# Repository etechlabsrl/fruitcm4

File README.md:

# Salmonberry Pi, Fruit \ 'früt \

> The Raspberry Pi is a series of credit card-sized single-board computers developed in the United Kingdom by the Raspberry Pi Foundation to promote the teaching of basic computer science in schools and developing countries. Official Link: [Raspberry Pi Foundation Homepage](https://raspberrypi.org), [Raspberry Pi Computer Homepage](https://www.raspberrypi.com)

<p>

Salmonberry Pi is a group of open source hardware projects which allow the construction of cluster hardware from small to arbitrary size using Raspberry Pi platforms.  This includes the Raspberry Pi Compute Module 4 (CM4) Raspberry Pi Zero 2 W, Raspberry Pi 4 Model B, and Raspberry Pi RP2040 microcontrollers.

The goals of this project are to provide:
- infrastructure for clustering nodes
- self-sufficient nodes by default (no 'leader')
- remotely monitoring
- remote management
- standard form factors and connectors, although perhaps repurposed

The component projects are:
- [Face CM4](https://github.com/salmonberrypi/facecm4), 8TE 3U faceplate with jacks, microSD card slot and LEDs.
- [Fruit CM4](https://github.com/salmonberrypi/fruitcm4), carrier board for CM4, general purpose compute or storage or both.
- [Graft](https://github.com/salmonberrypi/graft), development board to bring up Fruit board, allows diversion to on-board connectors for rhizome served power and signals. Can be used with or without rhizome boards. (out of date)
- [Thorn](https://github.com/salmonberrypi/thorn), passive board to protect the male plug on the Fruit or Graft boards. (out of date)
- [Rhizome](https://github.com/salmonberrypi/rhizome), life support systems and connectivity
- [Stem 3U x 160mm](https://github.com/salmonberrypi/stem_3U_160mm_X4), 3U x 160mm passive slot extension for debugging

(images are from a previous revision and out of date, shown for reference)

PCB front:

PCB back:

Dimensions: 160 x 100mm (0.562 x 0.478 [bananas](http://bananaforscale.info/#!/convert/length/bananas/millimeters)) without connector and faceplate, 4 layer PCB (pwr/signal, gnd, gnd, pwr/signal).

Review [Interactive BOM](https://htmlpreview.github.io/?https://raw.githubusercontent.com/salmonberrypi/fruitcm4/main/artifacts/bom/ibom.html).

Review [Schematic](https://github.com/salmonberrypi/fruitcm4/blob/main/artifacts/fruitcm4%20schematic.pdf).

---

Designed in [KiCad 6](https://kicad.org) on [Ubuntu](https://ubuntu.org) 21.10 (impish).

---

Raspberry Pi is a trademark of Raspberry Pi Trading

---

Copyright (C) 2022 Christian Kuhtz

This source describes Open Hardware and is licensed under the CERN-OHLW v2
<P>
You may redistribute and modify this documentation and make products
using it under the terms of the CERN-OHL-W v2 (https:/cern.ch/cern-ohl).
<P>
This documentation is distributed WITHOUT ANY EXPRESS OR IMPLIED
WARRANTY, INCLUDING OF MERCHANTABILITY, SATISFACTORY QUALITY
AND FITNESS FOR A PARTICULAR PURPOSE. Please see the <a href="https://ohwr.org/cern_ohl_w_v2.txt">CERN-OHL-W v2</a> for applicable conditions.
<P>
Source location: https://github.com/salmonberrypi
<P>
As per CERN-OHL-W v2 section 4.1, should You produce hardware based on
these sources, You must maintain the Source Location visible on the
external case of the Salmonberry Pi or other product you make using
this documentation.

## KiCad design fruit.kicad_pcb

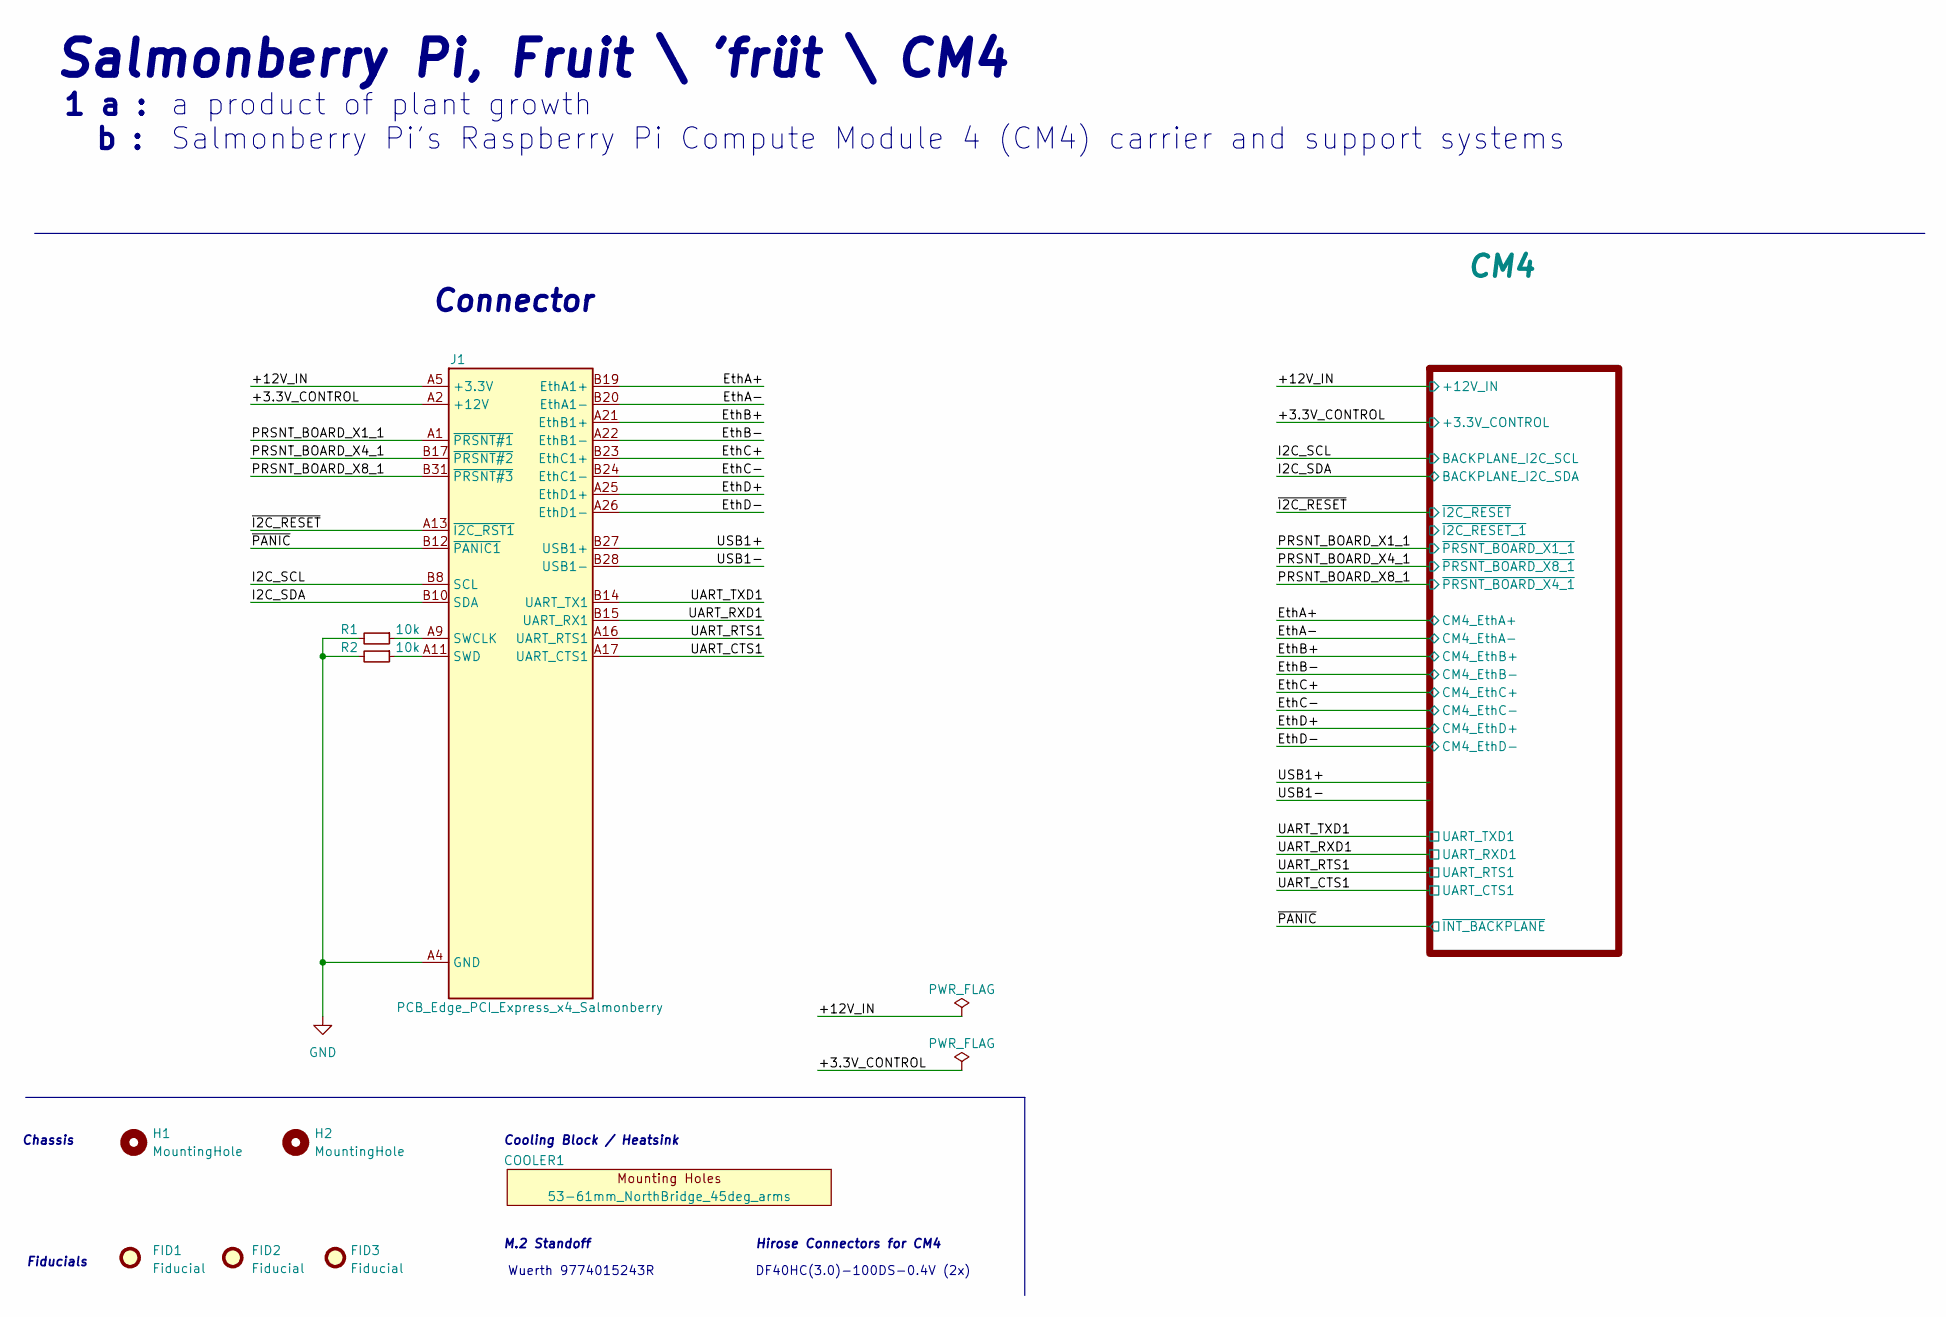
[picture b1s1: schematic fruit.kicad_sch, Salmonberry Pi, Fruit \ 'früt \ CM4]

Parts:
COOLER1: 53-61mm_NorthBridge_45deg_arms
FID1, FID2, FID3: Fiducial; Fiducial_1mm_Mask2mm
H1, H2: MountingHole; MountingHole_2.7mm_M2.5
J1: PCB_Edge_PCI_Express_x4_Salmonberry; BUS_PCIexpress_x4_Salmonberry_reduced_shoulders
R1, R2: 10k; R_0402_1005Metric

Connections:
+3.3V: J1.A5 (+3.3V), J1.A6 (+3.3V), J1.B5 (+3.3V), J1.B6 (+3.3V); also elsewhere on the board
+12V: J1.A2 (+12V), J1.A3 (+12V), J1.B1 (+12V), J1.B2 (+12V), J1.B3 (+12V); also elsewhere on the board
/EthA+: J1.B19 (EthA1+); also elsewhere on the board
/EthA-: J1.B20 (EthA1-); also elsewhere on the board
/EthB+: J1.A21 (EthB1+); also elsewhere on the board
/EthB-: J1.A22 (EthB1-); also elsewhere on the board
/EthC+: J1.B23 (EthC1+); also elsewhere on the board
/EthC-: J1.B24 (EthC1-); also elsewhere on the board
/EthD+: J1.A25 (EthD1+); also elsewhere on the board
/EthD-: J1.A26 (EthD1-); also elsewhere on the board
/I2C_SCL: J1.B8 (SCL); also elsewhere on the board
/I2C_SDA: J1.B10 (SDA); also elsewhere on the board
/PRSNT_BOARD_X1_1: J1.A1 (~PRSNT#1); also elsewhere on the board
/PRSNT_BOARD_X4_1: J1.B17 (~PRSNT#2); also elsewhere on the board
/PRSNT_BOARD_X8_1: J1.B31 (~PRSNT#3); also elsewhere on the board
/UART_CTS1: J1.A17 (UART_CTS1); also elsewhere on the board
/UART_RTS1: J1.A16 (UART_RTS1); also elsewhere on the board
/UART_RXD1: J1.B15 (UART_RX1); also elsewhere on the board
/UART_TXD1: J1.B14 (UART_TX1); also elsewhere on the board
/USB1+: J1.B27 (USB1+)
/USB1-: J1.B28 (USB1-)
/~I2C_RESET: J1.A13 (~I2C_RST1); also elsewhere on the board
/~PANIC: J1.B12 (~PANIC1); also elsewhere on the board
GND: J1.A4 (GND), J1.A7 (GND), J1.A8 (GND), J1.A10 (GND), J1.A12 (GND), J1.A14 (GND), J1.A15 (GND), J1.A18 (GND), J1.A19 (GND), J1.A20 (GND), J1.A23 (GND), J1.A24 (GND), J1.A27 (GND), J1.A28 (GND), J1.A29 (GND), J1.A30 (GND), J1.A31 (GND), J1.A32 (GND), J1.B4 (GND), J1.B7 (GND), J1.B9 (GND), J1.B11 (GND), J1.B13 (GND), J1.B16 (GND), J1.B18 (GND), J1.B21 (GND), J1.B22 (GND), J1.B25 (GND), J1.B26 (GND), J1.B29 (GND), J1.B30 (GND), J1.B32 (GND), R1.2, R2.2; also elsewhere on the board
unnamed: J1.A9 (SWCLK), R1.1
unnamed: J1.A11 (SWD), R2.1

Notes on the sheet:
Cooling Block / Heatsink
M.2 Standoff
Salmonberry Pi, Fruit \ 'früt \ CM4
Fiducials
1 a : b :
a product of plant growth Salmonberry Pi's Raspberry Pi Compute Module 4 (CM4) carrier and support systems
Hirose Connectors for CM4
DF40HC(3.0)-100DS-0.4V (2x)
Chassis
Wuerth 9774015243R
Connector

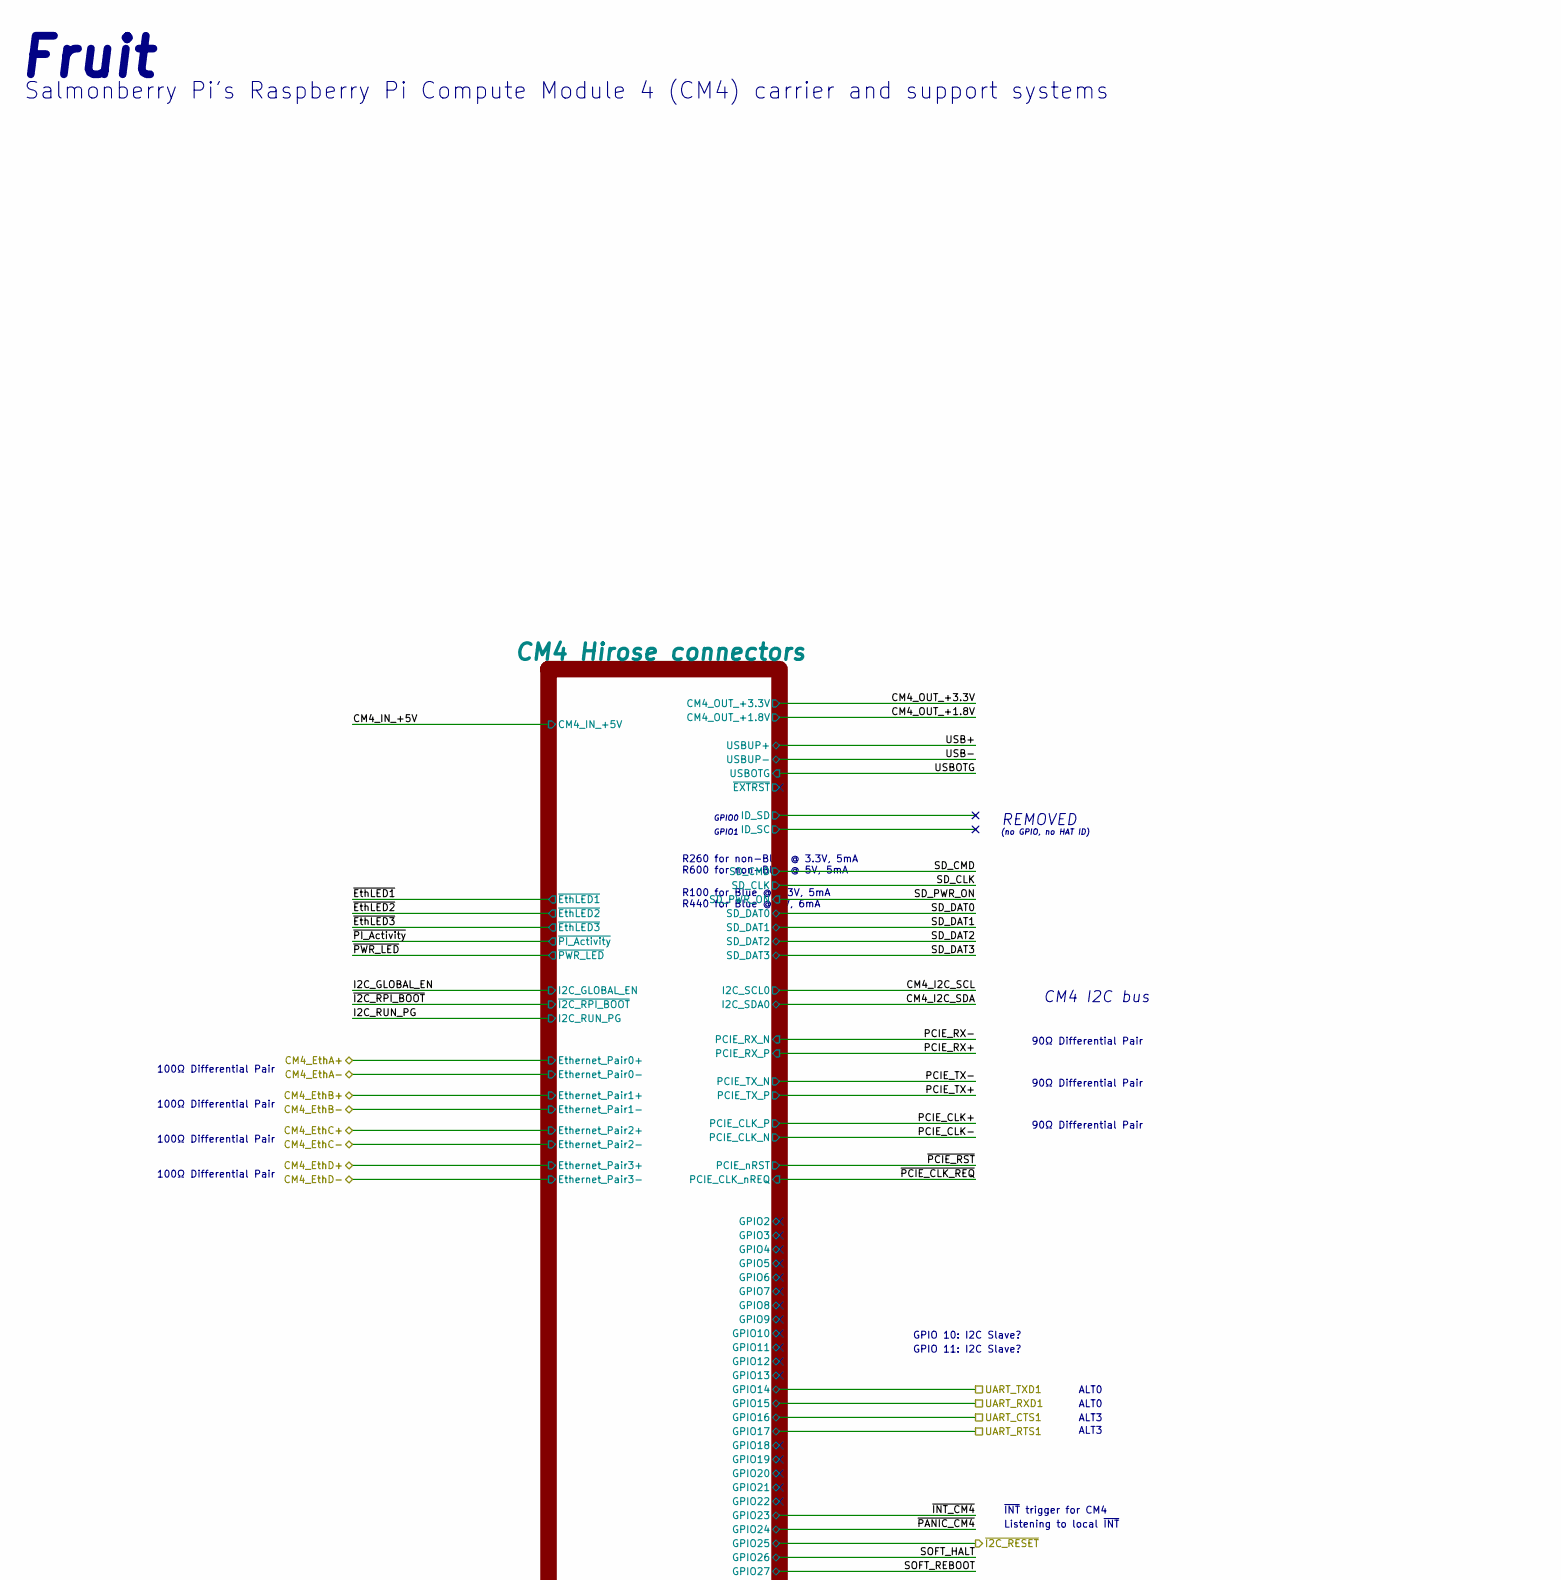
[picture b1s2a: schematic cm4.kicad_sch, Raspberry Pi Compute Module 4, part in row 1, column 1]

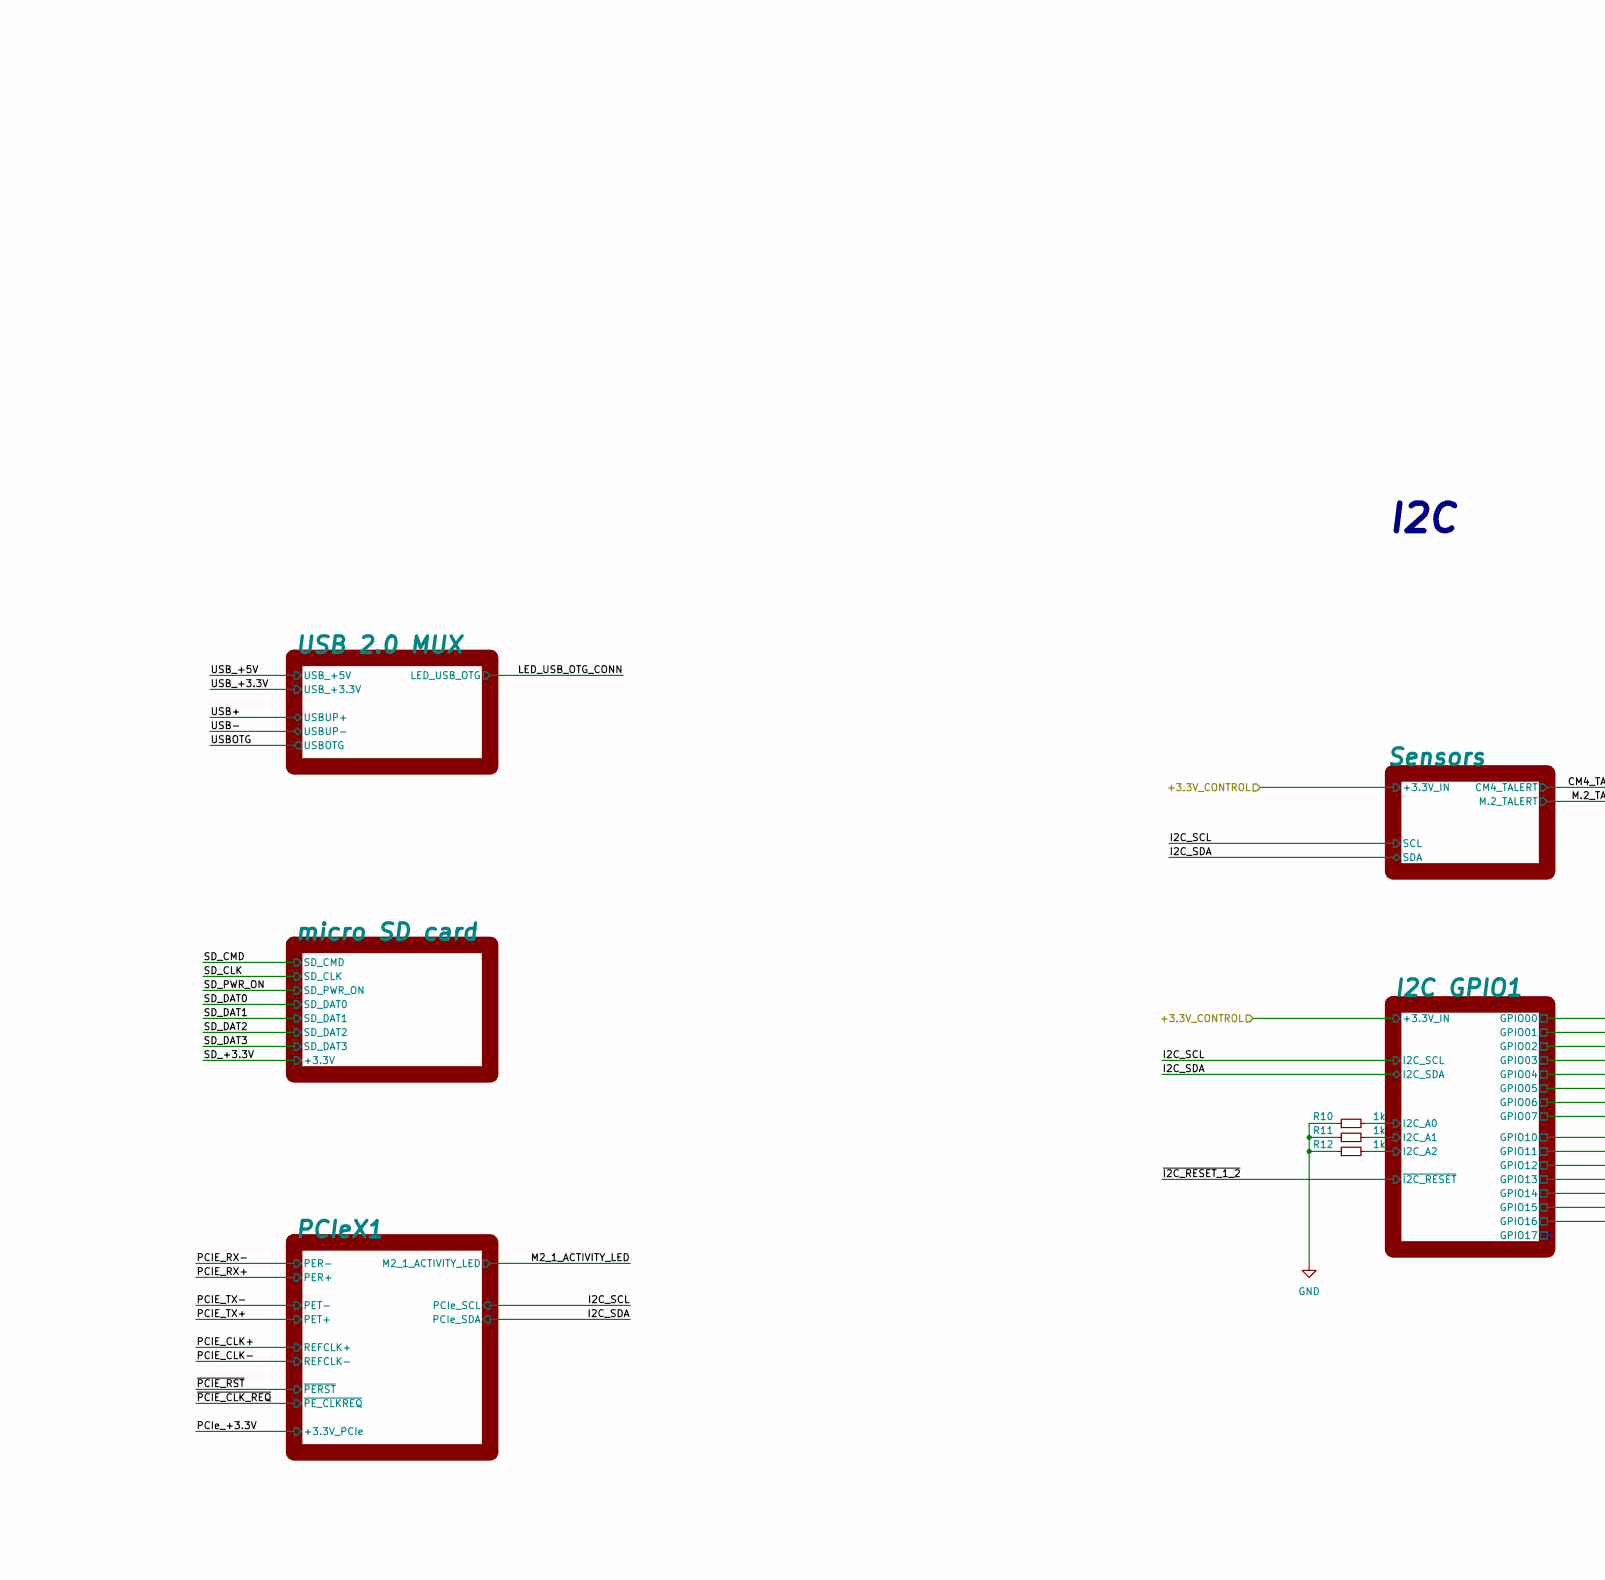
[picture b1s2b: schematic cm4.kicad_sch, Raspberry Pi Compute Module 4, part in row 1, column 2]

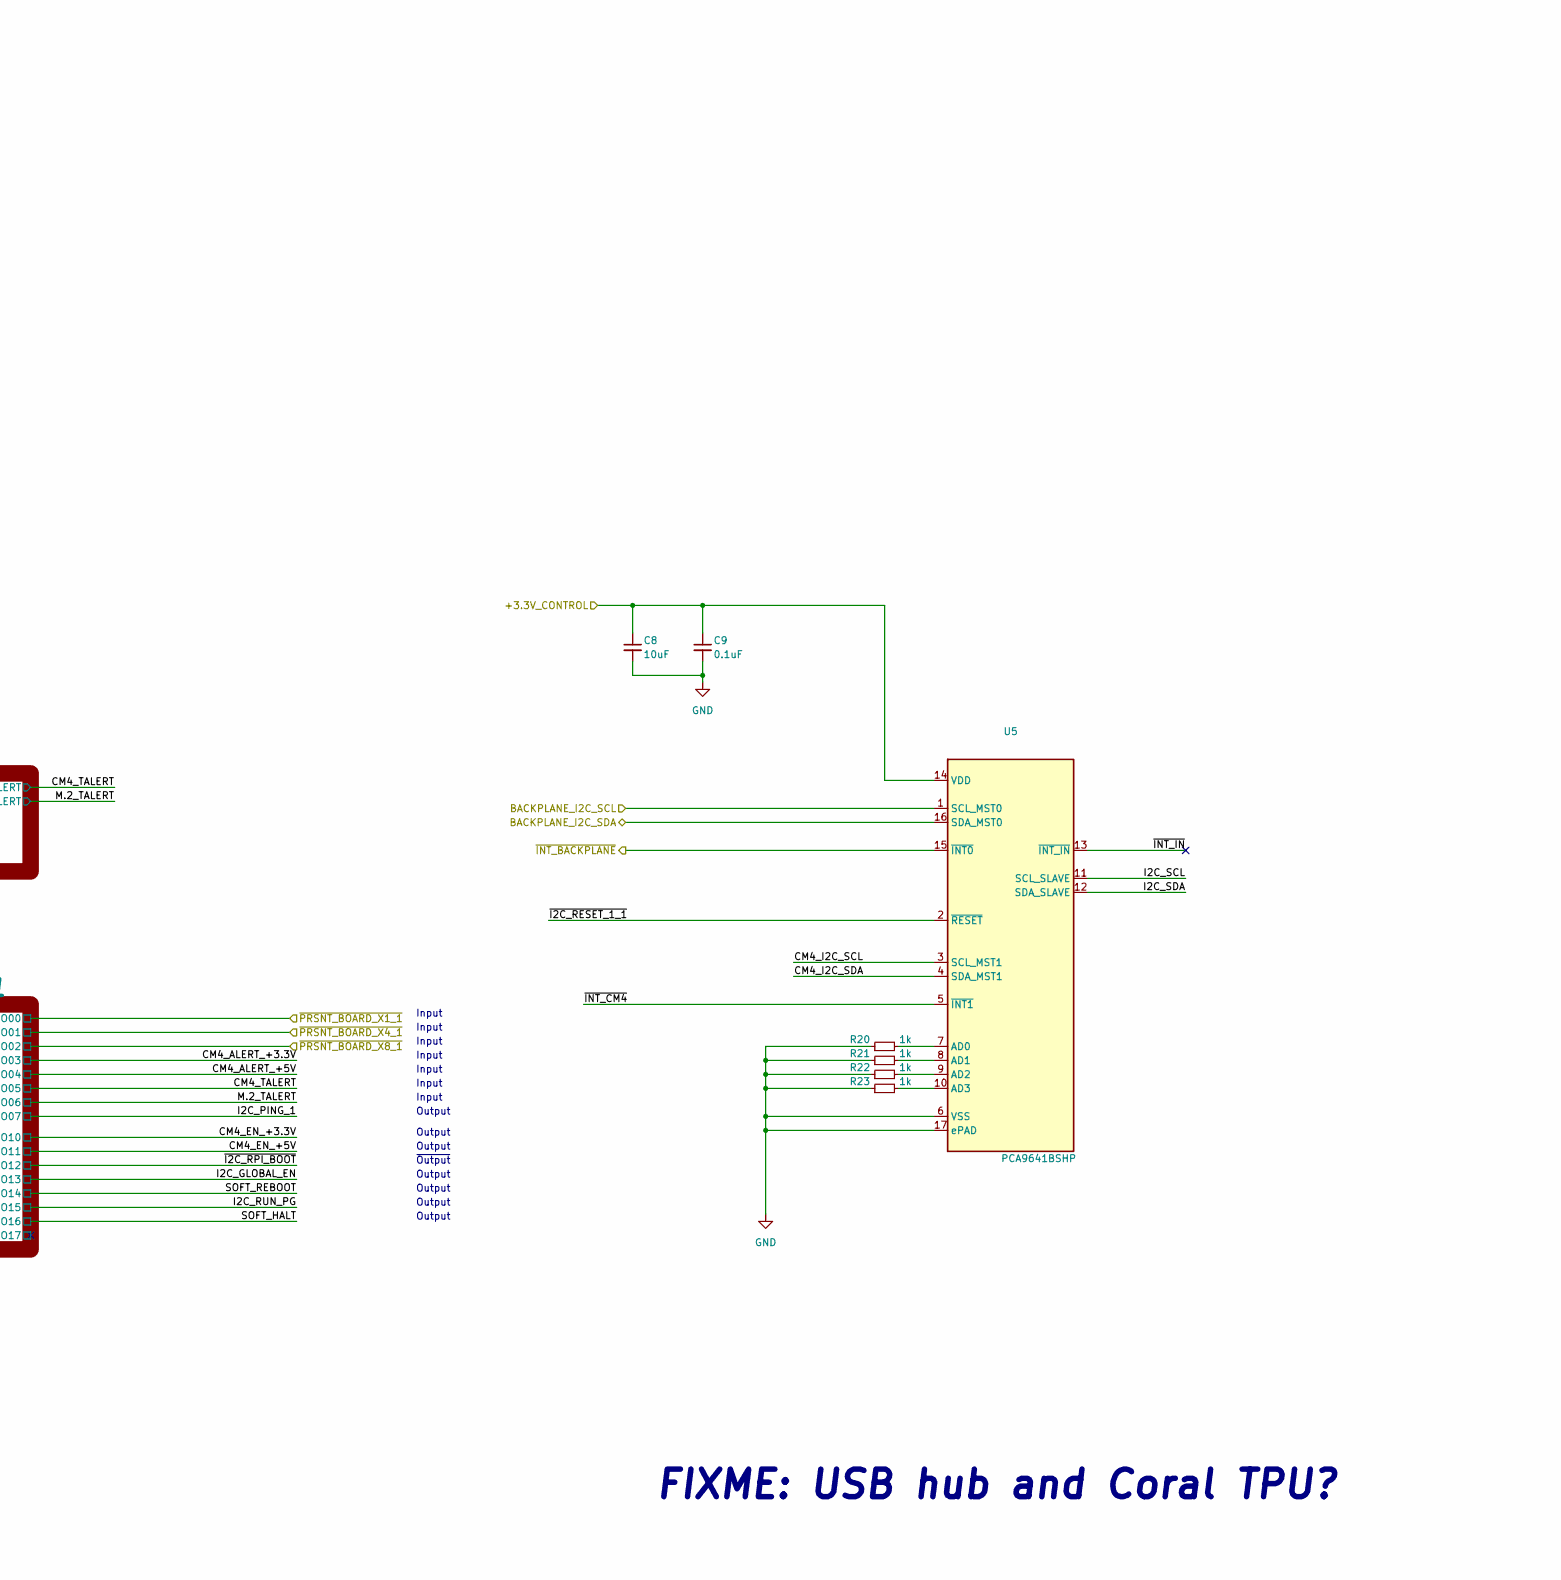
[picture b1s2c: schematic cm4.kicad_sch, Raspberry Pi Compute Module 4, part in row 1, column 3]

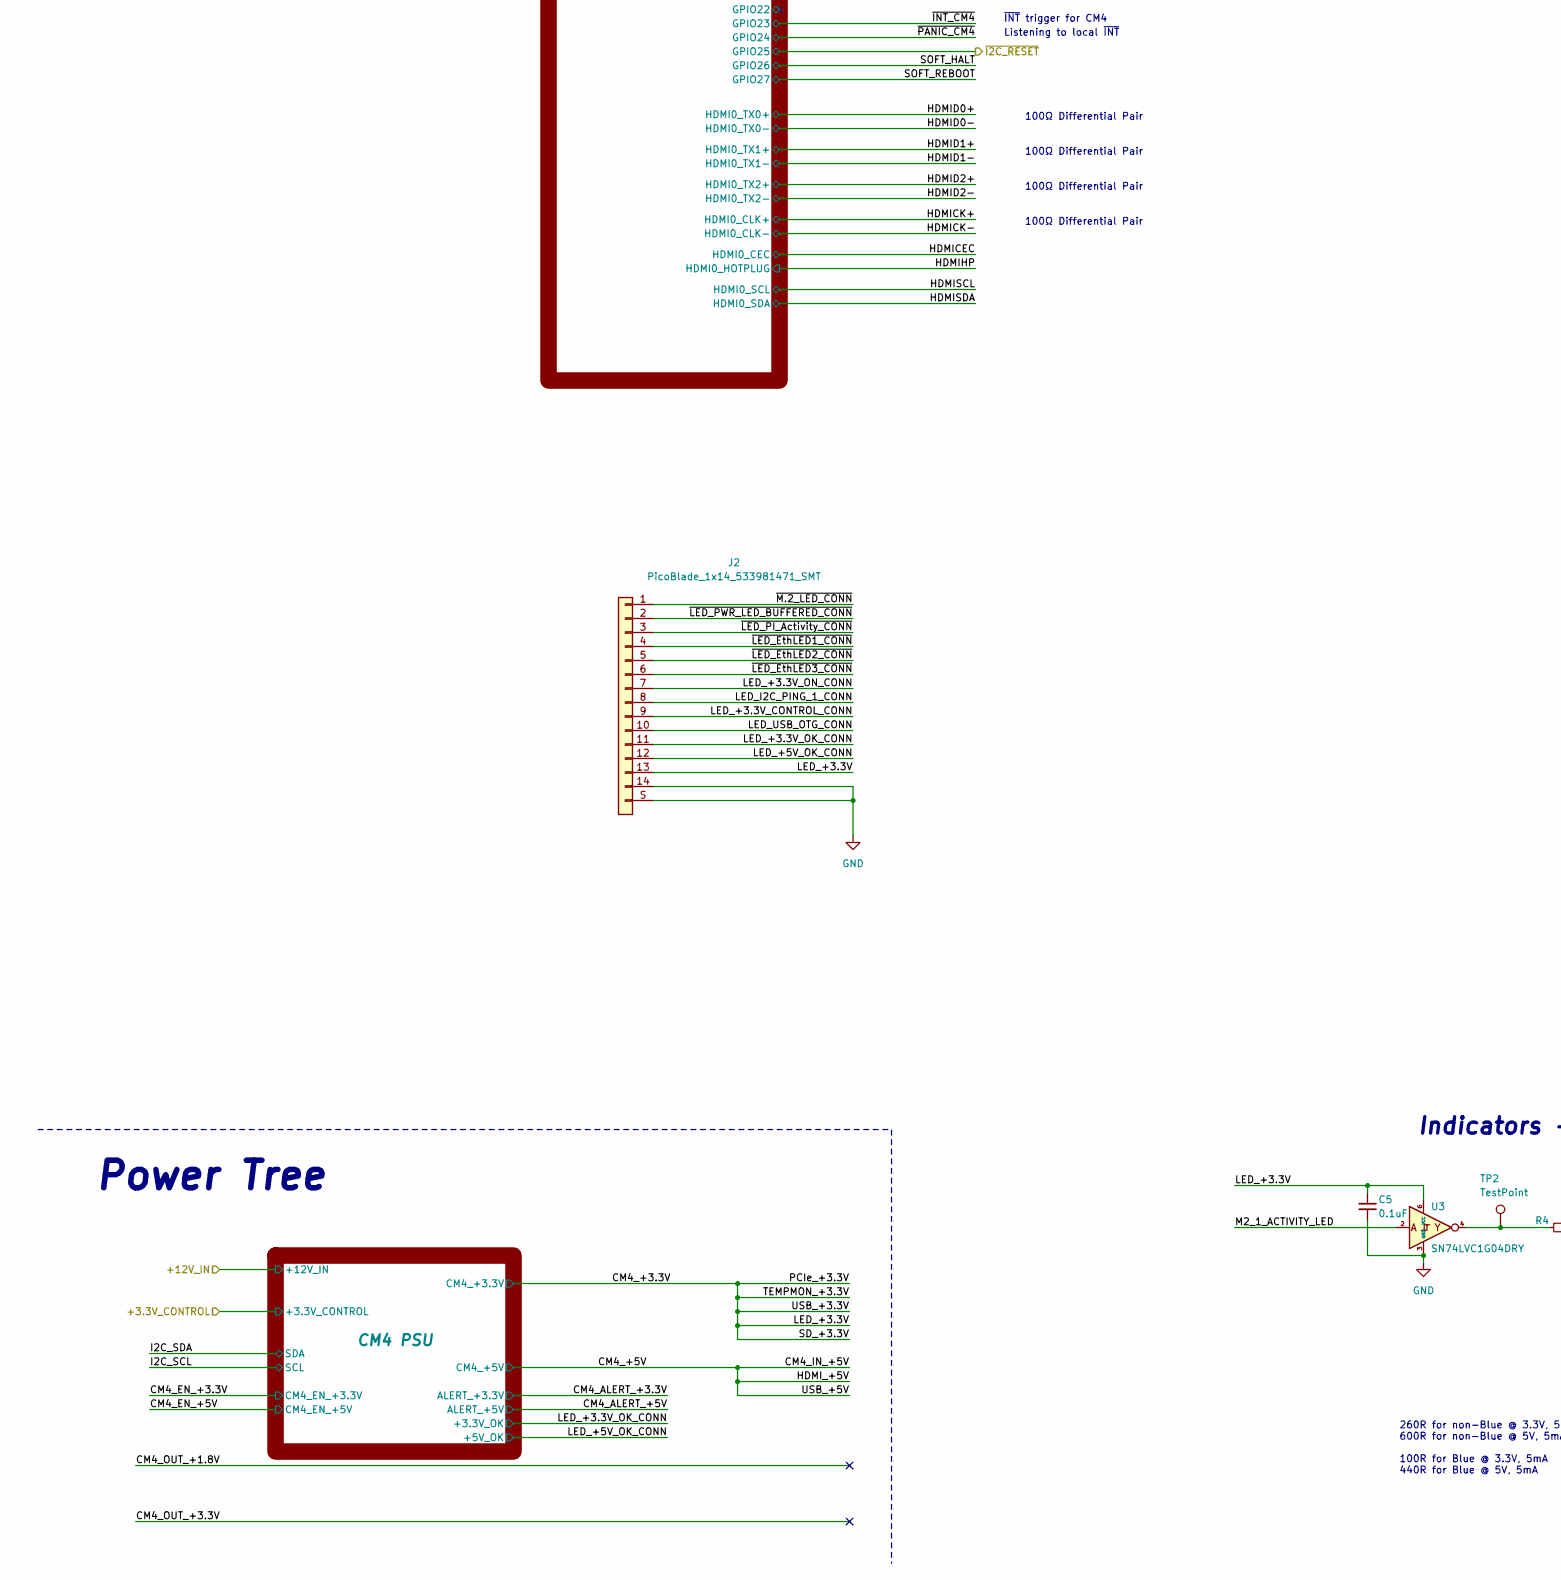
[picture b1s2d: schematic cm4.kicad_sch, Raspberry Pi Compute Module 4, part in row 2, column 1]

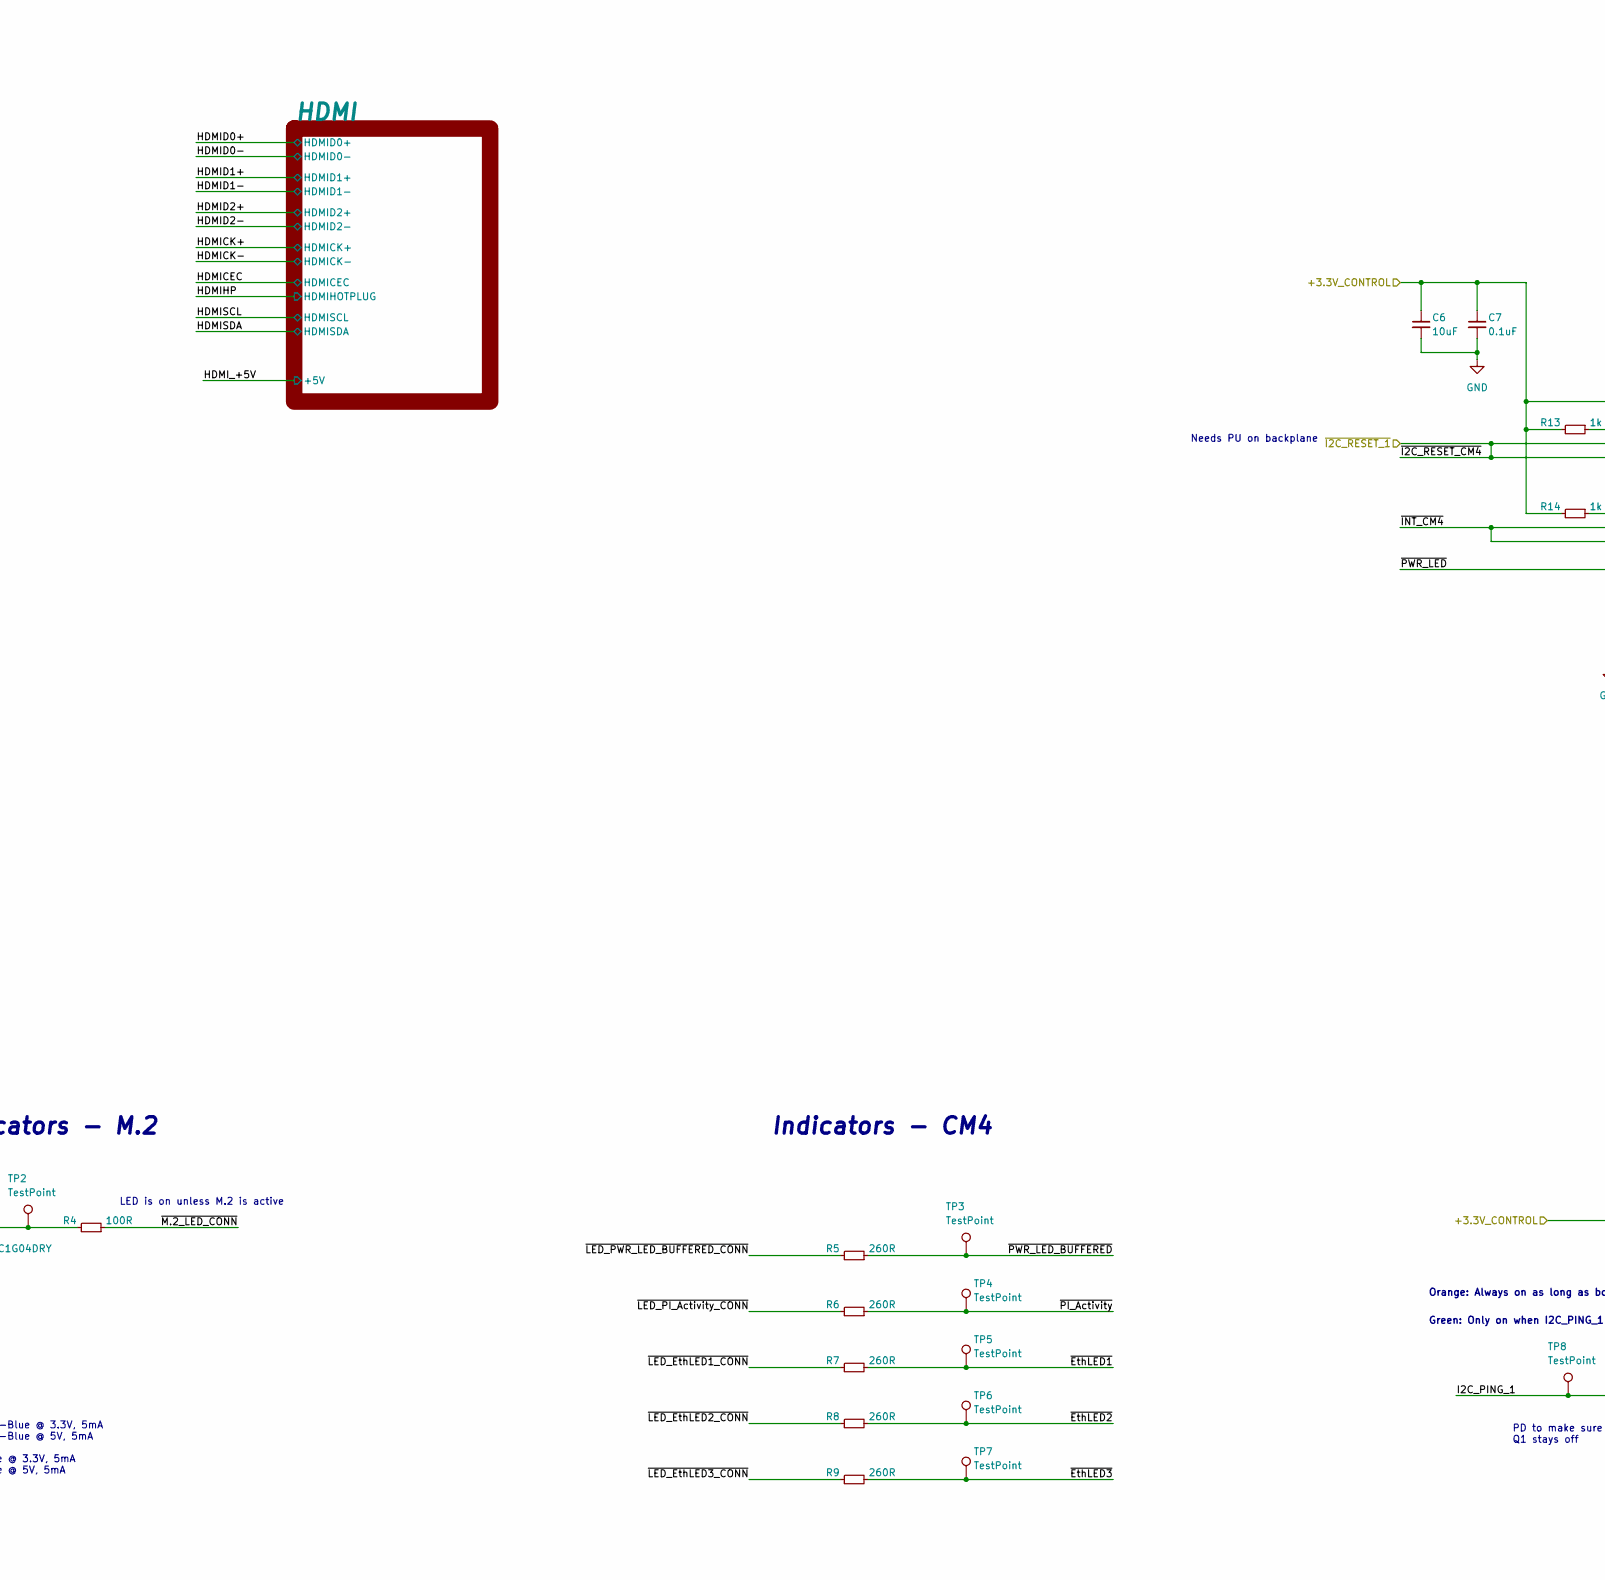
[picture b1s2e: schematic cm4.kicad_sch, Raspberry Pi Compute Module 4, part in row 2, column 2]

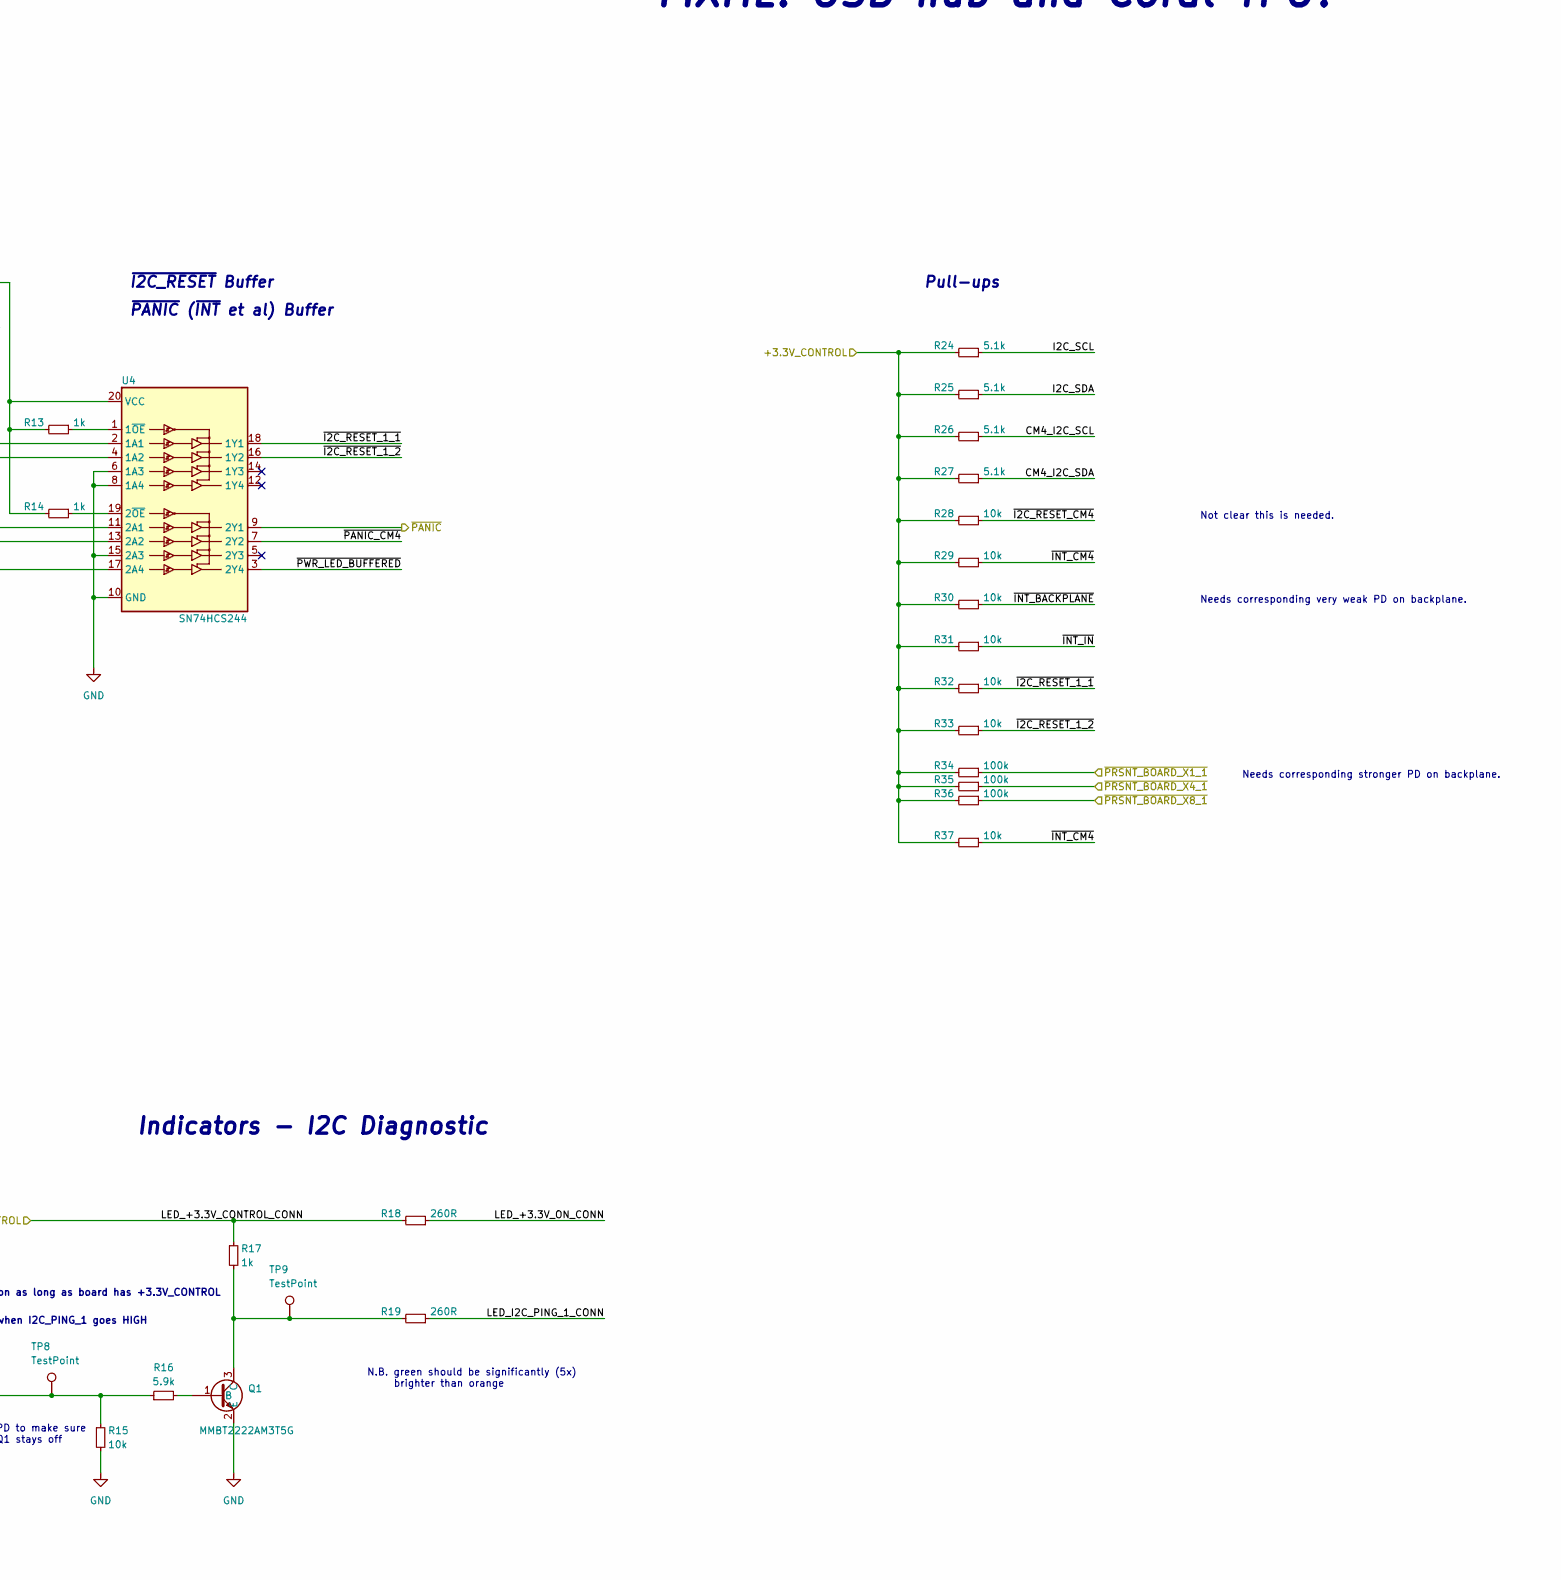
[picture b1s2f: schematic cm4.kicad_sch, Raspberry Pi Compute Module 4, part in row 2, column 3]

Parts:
C5, C7, C9: 0.1uF; C_0402_1005Metric
C6, C8: 10uF; C_0402_1005Metric
J2: PicoBlade_1x14_533981471_SMT; MOLEX_533981471; MPN 533981471
Q1: MMBT2222AM3T5G; MPN MMBT2222AM3T5G
R4: 100R; R_0402_1005Metric
R5, R6, R7, R8, R9, R18, R19: 260R; R_0402_1005Metric
R10, R11, R12, R13, R14, R17, R20, R21, R22, R23: 1k; R_0402_1005Metric
R15, R28, R29, R30, R31, R32, R33, R37: 10k; R_0402_1005Metric
R16: 5.9k; R_0402_1005Metric
R24, R25, R26, R27: 5.1k; R_0402_1005Metric
R34, R35, R36: 100k; R_0402_1005Metric
TP2, TP3, TP4, TP5, TP6, TP7, TP8, TP9: TestPoint; TestPoint_Pad_D1.0mm
U3: SN74LVC1G04DRY; PSON50P145X100X60-6N-DRY0006A; MPN SN74LVC1G04DRY
U4: SN74HCS244; RKS0020A; MPN SN74HCS244RKSR
U5: PCA9641BSHP; SOT758-1_HVQFN-16_3x3mm_P0.5mm_EP1.75x1.75mm_NXP; MPN PCA9641BSHP

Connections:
+12V: C6.1, C7.1, C8.1, C9.1, J2.9, R13.2, R14.2, R17.1, R18.2, R24.2, R25.2, R26.2, R27.2, R28.2, R29.2, R30.2, R31.2, R32.2, R33.2, R34.2, R35.2, R36.2, R37.2, U4.20 (VCC), U5.14 (VDD); also elsewhere on the board
/CM4/CM4_+3.3V: C5.1, J2.13, U3.6 (VCC); also elsewhere on the board
/CM4/CM4_I2C_SCL: R26.1, U5.3 (SCL_MST1); also elsewhere on the board
/CM4/CM4_I2C_SDA: R27.1, U5.4 (SDA_MST1); also elsewhere on the board
/CM4/I2C GPIO1/I2C_A0: R10.2; also elsewhere on the board
/CM4/I2C GPIO1/I2C_A1: R11.2; also elsewhere on the board
/CM4/I2C GPIO1/I2C_A2: R12.2; also elsewhere on the board
/CM4/I2C_PING_1: R15.1, R16.1, TP8.1; also elsewhere on the board
/CM4/I2C_SCL: R24.1, U5.11 (SCL_SLAVE); also elsewhere on the board
/CM4/I2C_SDA: R25.1, U5.12 (SDA_SLAVE); also elsewhere on the board
/CM4/LED_+3.3V_OK_CONN: J2.11; also elsewhere on the board
/CM4/LED_+3.3V_ON_CONN: J2.7, R18.1
/CM4/LED_+5V_OK_CONN: J2.12; also elsewhere on the board
/CM4/LED_I2C_PING_1_CONN: J2.8, R19.1
/CM4/LED_USB_OTG_CONN: J2.10; also elsewhere on the board
/CM4/M2_1_ACTIVITY_LED: U3.2; also elsewhere on the board
/CM4/~EthLED1: R7.2, TP5.1; also elsewhere on the board
/CM4/~EthLED2: R8.2, TP6.1; also elsewhere on the board
/CM4/~EthLED3: R9.2, TP7.1; also elsewhere on the board
/CM4/~I2C_RESET_1_1: R32.1, U4.18 (1Y1), U5.2 (~RESET)
/CM4/~I2C_RESET_1_2: R33.1, U4.16 (1Y2); also elsewhere on the board
/CM4/~I2C_RESET_CM4: R28.1, U4.2 (1A1), U4.4 (1A2)
/CM4/~INT_CM4: R29.1, R37.1, U4.11 (2A1), U4.13 (2A2), U5.5 (~INT1); also elsewhere on the board
/CM4/~INT_IN: R31.1, U5.13 (~INT_IN)
/CM4/~LED_EthLED1_CONN: J2.4, R7.1
/CM4/~LED_EthLED2_CONN: J2.5, R8.1
/CM4/~LED_EthLED3_CONN: J2.6, R9.1
/CM4/~LED_PI_Activity_CONN: J2.3, R6.2
/CM4/~LED_PWR_LED_BUFFERED_CONN: J2.2, R5.2
/CM4/~M.2_LED_CONN: J2.1, R4.1
/CM4/~PANIC_CM4: U4.7 (2Y2); also elsewhere on the board
/CM4/~PANIC: U4.9 (2Y1)
/CM4/~PI_Activity: R6.1, TP4.1; also elsewhere on the board
/CM4/~PWR_LED_BUFFERED: R5.1, TP3.1, U4.3 (2Y4)
/CM4/~PWR_LED: U4.17 (2A4); also elsewhere on the board
/I2C_SCL: U5.1 (SCL_MST0); also elsewhere on the board
/I2C_SDA: U5.16 (SDA_MST0); also elsewhere on the board
/PRSNT_BOARD_X1_1: R34.1; also elsewhere on the board
/PRSNT_BOARD_X4_1: R36.1; also elsewhere on the board
/PRSNT_BOARD_X8_1: R35.1; also elsewhere on the board
/~PANIC: R30.1, U5.15 (~INT0); also elsewhere on the board
GND: C5.2, C6.2, C7.2, C8.2, C9.2, J2.14, J2.S (SHIELD), Q1.2 (E), R10.1, R11.1, R12.1, R15.2, R20.1, R21.1, R22.1, R23.1, U3.3 (GND), U4.6 (1A3), U4.8 (1A4), U4.10 (GND), U4.15 (2A3), U4.21 (ePAD), U5.6 (VSS), U5.17 (ePAD); also elsewhere on the board
unnamed: Q1.1 (B), R16.2
unnamed: Q1.3 (C), R17.2, R19.2, TP9.1
unnamed: R4.2, TP2.1, U3.4
unnamed: R13.1, U4.1 (1~OE)
unnamed: R14.1, U4.19 (2~OE)
unnamed: R20.2, U5.7 (AD0)
unnamed: R21.2, U5.8 (AD1)
unnamed: R22.2, U5.9 (AD2)
unnamed: R23.2, U5.10 (AD3)

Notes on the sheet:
I2C
Output
100Ω Differential Pair
~{Output}
Orange: Always on as long as board has +3.3V_CONTROL
90Ω Differential Pair
(no GPIO, no HAT ID)
Indicators - I2C Diagnostic
ALT0
Input
Listening to local ~{INT}
GPIO 10: I2C Slave?
REMOVED
Needs PU on backplane
~{PANIC} (~{INT} et al) Buffer
ALT3
~{I2C_RESET} Buffer
PD to make sure Q1 stays off
Pull-ups
~{INT} trigger for CM4
N.B. green should be significantly (5x) brighter than orange
Indicators - CM4
Salmonberry Pi's Raspberry Pi Compute Module 4 (CM4) carrier and support systems
260R for non-Blue @ 3.3V, 5mA 600R for non-Blue @ 5V, 5mA 100R for Blue @ 3.3V, 5mA 440R for Blue @ 5V, 5mA
FIXME: USB hub and Coral TPU?
Needs corresponding very weak PD on backplane.
Green: Only on when I2C_PING_1 goes HIGH
R260 for non-Blue @ 3.3V, 5mA R600 for non-Blue @ 5V, 5mA R100 for Blue @ 3.3V, 5mA R440 for Blue @ 5V, 6mA
GPIO 11: I2C Slave?
Needs corresponding stronger PD on backplane.
Fruit
GPIO1
Indicators - M.2
Power Tree
Not clear this is needed.
GPIO0
CM4 I2C bus
LED is on unless M.2 is active

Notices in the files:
cm4.kicad_sch:
Copyright © 2022 Christian Kuhtz
CERN-OHL-W v2 or later
